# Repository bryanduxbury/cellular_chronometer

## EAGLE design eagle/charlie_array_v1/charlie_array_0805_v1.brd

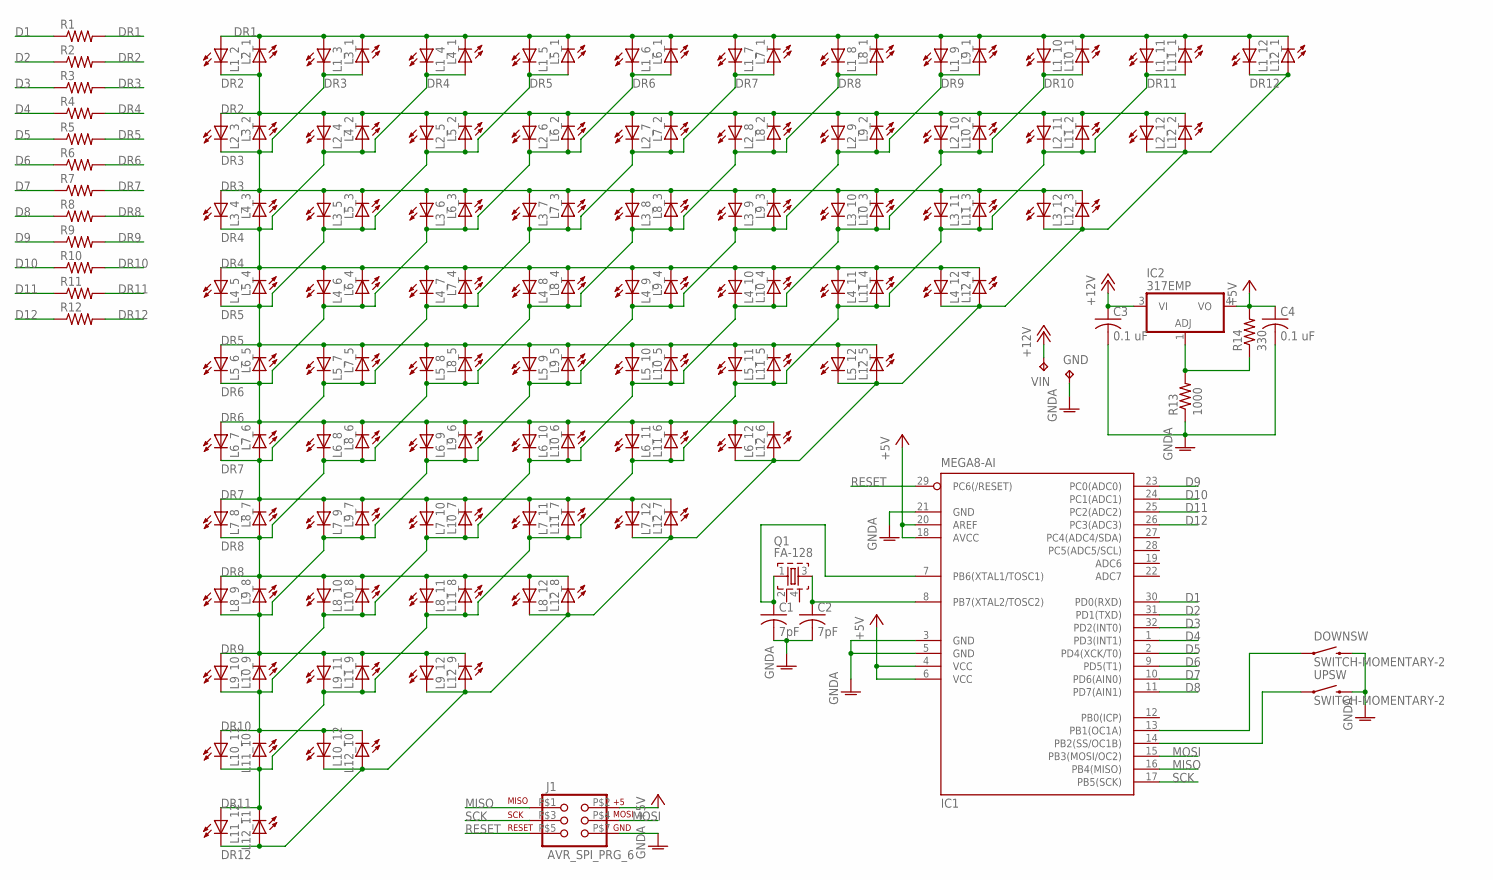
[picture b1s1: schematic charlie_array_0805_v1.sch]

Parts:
C1, C2: 7pF; C0603
C3, C4: 0.1 uF; C0603
DOWNSW: SWITCH-MOMENTARY-2; TACTILE_SWITCH_TALL
GND: TPTP20SQ; TP20SQ
IC1: MEGA8-AI; TQFP32-08
IC2: 317EMP; SOT223
J1: AVR_SPI_PRG_6; 2X3_ICSP_SMD
L1_2, L1_3, L1_4, L1_5, L1_6, L1_7, L1_8, L1_9, L1_10, L1_11, L1_12, L2_1, L2_3, L2_4, L2_5, L2_6, L2_7, L2_8, L2_9, L2_10, L2_11, L2_12, L3_1, L3_2, L3_4, L3_5, L3_6, L3_7, L3_8, L3_9, L3_10, L3_11, L3_12, L4_1, L4_2, L4_3, L4_5, L4_6, L4_7, L4_8, L4_9, L4_10, L4_11, L4_12, L5_1, L5_2, L5_3, L5_4, L5_6, L5_7, L5_8, L5_9, L5_10, L5_11, L5_12, L6_1, L6_2, L6_3, L6_4, L6_5, L6_7, L6_8, L6_9, L6_10, L6_11, L6_12, L7_1, L7_2, L7_3, L7_4, L7_5, L7_6, L7_8, L7_9, L7_10, L7_11, L7_12, L8_1, L8_2, L8_3, L8_4, L8_5, L8_6, L8_7, L8_9, L8_10, L8_11, L8_12, L9_1, L9_2, L9_3, L9_4, L9_5, L9_6, L9_7, L9_8, L9_10, L9_11, L9_12, L10_1, L10_2, L10_3, L10_4, L10_5, L10_6, L10_7, L10_8, L10_9, L10_11, L10_12, L11_1, L11_2, L11_3, L11_4, L11_5, L11_6, L11_7, L11_8, L11_9, L11_10, L11_12, L12_1, L12_2, L12_3, L12_4, L12_5, L12_6, L12_7, L12_8, L12_9, L12_10, L12_11: LEDCHIPLED_0805; CHIPLED_0805
Q1: FA-128
R1, R2, R3, R4, R5, R6, R7, R8, R9, R10, R11, R12: R-US_R0603; R0603
R13: 1000; R0603
R14: 330; R0603
UPSW: SWITCH-MOMENTARY-2; TACTILE_SWITCH_TALL
VIN: TPTP20SQ; TP20SQ

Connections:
+5V: C4.1, IC1.4 (VCC), IC1.6 (VCC), IC1.18 (AVCC), IC1.20 (AREF), IC2.4 (VO), J1.P$2 (2), R14.2
+12V: C3.1, IC2.3 (VI), VIN.TP
D1: IC1.30 (PD0(RXD)), R1.1
D2: IC1.31 (PD1(TXD)), R2.1
D3: IC1.32 (PD2(INT0)), R3.1
D4: IC1.1 (PD3(INT1)), R4.1
D5: IC1.2 (PD4(XCK/T0)), R5.1
D6: IC1.9 (PD5(T1)), R6.1
D7: IC1.10 (PD6(AIN0)), R7.1
D8: IC1.11 (PD7(AIN1)), R8.1
D9: IC1.23 (PC0(ADC0)), R9.1
D10: IC1.24 (PC1(ADC1)), R10.1
D11: IC1.25 (PC2(ADC2)), R11.1
D12: IC1.26 (PC3(ADC3)), R12.1
DR1: L1_2.A, L1_3.A, L1_4.A, L1_5.A, L1_6.A, L1_7.A, L1_8.A, L1_9.A, L1_10.A, L1_11.A, L1_12.A, L2_1.C, L3_1.C, L4_1.C, L5_1.C, L6_1.C, L7_1.C, L8_1.C, L9_1.C, L10_1.C, L11_1.C, L12_1.C, R1.2
DR2: L1_2.C, L2_1.A, L2_3.A, L2_4.A, L2_5.A, L2_6.A, L2_7.A, L2_8.A, L2_9.A, L2_10.A, L2_11.A, L2_12.A, L3_2.C, L4_2.C, L5_2.C, L6_2.C, L7_2.C, L8_2.C, L9_2.C, L10_2.C, L11_2.C, L12_2.C, R2.2
DR3: L1_3.C, L2_3.C, L3_1.A, L3_2.A, L3_4.A, L3_5.A, L3_6.A, L3_7.A, L3_8.A, L3_9.A, L3_10.A, L3_11.A, L3_12.A, L4_3.C, L5_3.C, L6_3.C, L7_3.C, L8_3.C, L9_3.C, L10_3.C, L11_3.C, L12_3.C, R3.2
DR4: L1_4.C, L2_4.C, L3_4.C, L4_1.A, L4_2.A, L4_3.A, L4_5.A, L4_6.A, L4_7.A, L4_8.A, L4_9.A, L4_10.A, L4_11.A, L4_12.A, L5_4.C, L6_4.C, L7_4.C, L8_4.C, L9_4.C, L10_4.C, L11_4.C, L12_4.C, R4.2
DR5: L1_5.C, L2_5.C, L3_5.C, L4_5.C, L5_1.A, L5_2.A, L5_3.A, L5_4.A, L5_6.A, L5_7.A, L5_8.A, L5_9.A, L5_10.A, L5_11.A, L5_12.A, L6_5.C, L7_5.C, L8_5.C, L9_5.C, L10_5.C, L11_5.C, L12_5.C, R5.2
DR6: L1_6.C, L2_6.C, L3_6.C, L4_6.C, L5_6.C, L6_1.A, L6_2.A, L6_3.A, L6_4.A, L6_5.A, L6_7.A, L6_8.A, L6_9.A, L6_10.A, L6_11.A, L6_12.A, L7_6.C, L8_6.C, L9_6.C, L10_6.C, L11_6.C, L12_6.C, R6.2
DR7: L1_7.C, L2_7.C, L3_7.C, L4_7.C, L5_7.C, L6_7.C, L7_1.A, L7_2.A, L7_3.A, L7_4.A, L7_5.A, L7_6.A, L7_8.A, L7_9.A, L7_10.A, L7_11.A, L7_12.A, L8_7.C, L9_7.C, L10_7.C, L11_7.C, L12_7.C, R7.2
DR8: L1_8.C, L2_8.C, L3_8.C, L4_8.C, L5_8.C, L6_8.C, L7_8.C, L8_1.A, L8_2.A, L8_3.A, L8_4.A, L8_5.A, L8_6.A, L8_7.A, L8_9.A, L8_10.A, L8_11.A, L8_12.A, L9_8.C, L10_8.C, L11_8.C, L12_8.C, R8.2
DR9: L1_9.C, L2_9.C, L3_9.C, L4_9.C, L5_9.C, L6_9.C, L7_9.C, L8_9.C, L9_1.A, L9_2.A, L9_3.A, L9_4.A, L9_5.A, L9_6.A, L9_7.A, L9_8.A, L9_10.A, L9_11.A, L9_12.A, L10_9.C, L11_9.C, L12_9.C, R9.2
DR10: L1_10.C, L2_10.C, L3_10.C, L4_10.C, L5_10.C, L6_10.C, L7_10.C, L8_10.C, L9_10.C, L10_1.A, L10_2.A, L10_3.A, L10_4.A, L10_5.A, L10_6.A, L10_7.A, L10_8.A, L10_9.A, L10_11.A, L10_12.A, L11_10.C, L12_10.C, R10.2
DR11: L1_11.C, L2_11.C, L3_11.C, L4_11.C, L5_11.C, L6_11.C, L7_11.C, L8_11.C, L9_11.C, L10_11.C, L11_1.A, L11_2.A, L11_3.A, L11_4.A, L11_5.A, L11_6.A, L11_7.A, L11_8.A, L11_9.A, L11_10.A, L11_12.A, L12_11.C, R11.2
DR12: L1_12.C, L2_12.C, L3_12.C, L4_12.C, L5_12.C, L6_12.C, L7_12.C, L8_12.C, L9_12.C, L10_12.C, L11_12.C, L12_1.A, L12_2.A, L12_3.A, L12_4.A, L12_5.A, L12_6.A, L12_7.A, L12_8.A, L12_9.A, L12_10.A, L12_11.A, R12.2
GNDA: C1.2, C2.2, C3.2, C4.2, DOWNSW.B2 (2), GND.TP, IC1.3 (GND), IC1.5 (GND), IC1.21 (GND), J1.P$7 (6), R13.1, UPSW.B2 (2)
MISO: IC1.16 (PB4(MISO)), J1.P$1 (1)
MOSI: IC1.15 (PB3(MOSI/OC2)), J1.P$4 (4)
unnamed: C2.1, IC1.8 (PB7(XTAL2/TOSC2)), Q1.3
unnamed: IC1.14 (PB2(SS/OC1B)), UPSW.A2 (1)
unnamed: DOWNSW.A2 (1), IC1.13 (PB1(OC1A))
unnamed: C1.1, IC1.7 (PB6(XTAL1/TOSC1)), Q1.1
unnamed: IC2.1 (ADJ), R13.2, R14.1
RESET: IC1.29 (PC6(/RESET)), J1.P$5 (5)
SCK: IC1.17 (PB5(SCK)), J1.P$3 (3)

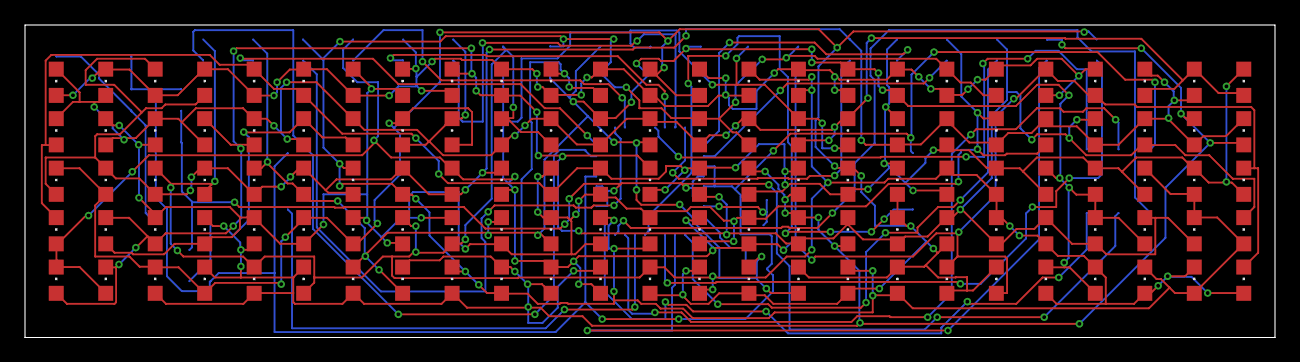
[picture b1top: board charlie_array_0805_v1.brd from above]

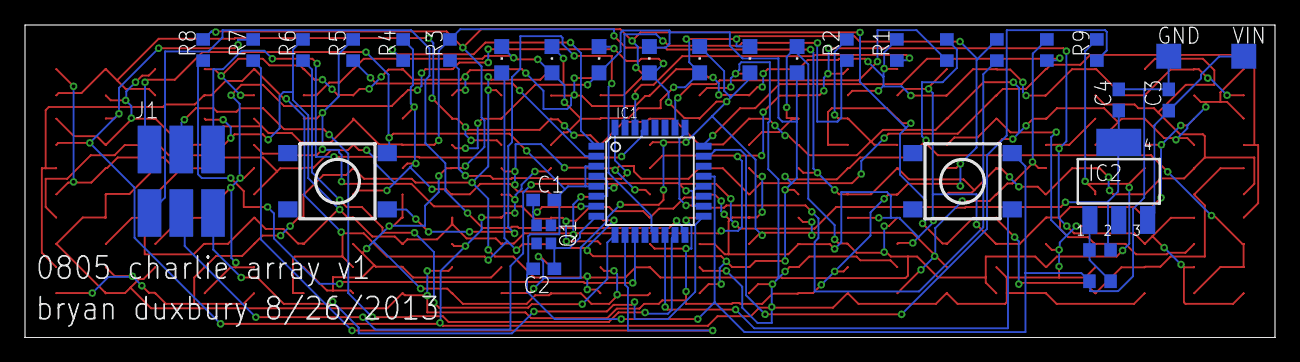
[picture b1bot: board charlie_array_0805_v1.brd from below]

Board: 2 copper layers, 100.0 x 25.0 mm, 158 parts (33 on the bottom side), 36 nets.

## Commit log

2013-07-02 init commit
2013-07-09 game of life prototype
2013-07-09 break out grid from proto, progress towards exploring for one prior generation
2013-07-10 added spec for basic grid behaviors; improved next_generation runtime by about 10x
2013-07-18 first stab at a genetic algo version of the predecessor search
2013-07-27 most of a working duparc predecessor searcher
2013-07-29 mostly? fixed a logical error in identifying the top row predecessors
2013-07-31 kinda working... making progress anyways
2013-07-31 nail down attributes of bounded/extra ataviser
2013-08-02 major improvements, particularly the intersecting row ataviser
2013-08-04 generated patterns for the narrow font
2013-08-04 add bitvector related stuff to Pt class
2013-08-04 mostly refactored on Pt methods
2013-08-04 gitignore time
2013-08-04 further refactorign
2013-08-05 searcher getting closer to working
2013-08-05 regen patterns
2013-08-05 don't need patterns.rb
2013-08-09 woo, have a full working display set
2013-08-13 lots of progress on chronomata sketch
2013-08-13 remove unused include
2013-08-16 added initial scad prototype, cleaned up some logic in sketch
2013-08-26 add gitignore
2013-08-26 eagle files v1
2013-08-26 adjusted to fit in 100mm width
2013-08-26 don't need these export files committed
2013-09-21 working out issues on the new hardware
2013-09-22 incremental progress
2013-09-27 figured out a bug in living_neighbors
2013-09-27 regen'd 2 back
2013-09-27 progress on firmware
2013-09-29 switched over to 32 bit masking instead of crazy looping
2013-10-02 remove concept of 'extra width' from row atavisers
2013-10-02 fix intersecting row ataviser spec
2013-10-02 incremental progress on enclosure design
2013-10-02 fix DuparcAtaviser to remove extra
2013-10-02 fix hierarchical duparc ataviser to remove extra
2013-10-08 changes to make search for toroidal grids; also, some performance improvements
2013-10-10 making first increments of progress on java version of ataviser
2013-10-11 some logging experiments in ruby search codebase
2013-10-11 java WIP
2013-10-12 closer to mimicking the ruby version of hierarchical ataviser
2013-10-12 add support for SolutionFilter
2013-10-12 test performance with TubularRowFilter
2013-10-12 add a little commenting to the core algorithm, and add smarter intermediate limiting
2013-10-12 add solution limiters
2013-10-12 oops, didn't want those compiled artifacts checked in at all
2013-10-12 move some stuff around in packages
2013-10-12 more repackaging
2013-10-13 introduce Grid class, modify everything to work with that
2013-10-13 oh yeah, RowAtaviser caching is important
2013-10-13 adding testing capabilities to Grid
2013-10-16 forward
2013-10-16 debugging through the issues with ruby toroidal solver
2013-10-17 experimenting with retaining many more intermediate solutions
2013-10-19 repackage... well, everything
2013-10-21 firmware progress
2013-10-23 cleaning up the firmware, ready to actually be tested
2013-10-23 all the ataviser's hard work
2013-10-23 don't need all the individual back_ files
2013-10-24 latest refactoring in ataviser
2013-10-26 fixed the issues with toroidal life (it's working now)
2013-10-26 extract a function
2013-10-26 clean up some cruft; latch the 'next state' button so it doesn't run faster than humans can see
2013-10-27 prototypes for nice linear fade in/out and crossfade effects
2013-10-27 gitignore .DS_Store
2013-10-27 remove some cruft; add the real deal method for advancing the clock minute by minute
2013-10-28 get rid of all the __back_* files
2013-10-28 recompute the goofed up 0100 priors
2013-10-28 fixed version of 01_00
2013-10-29 fixed conflict
2013-10-29 draft of seekUp() behavior
2013-10-29 woohoo, setting time through button press is working
2013-10-29 off by one error in fastMinuteDisplay
2013-10-29 added seekDown behavior
2013-10-29 get rid of the test driver loop
2013-10-30 oops, had a bug in seekDown()
2013-10-30 don't need this file anymore
2013-10-30 few little things to make display marginally faster
2013-10-30 remove the clear() call inside fastDisplayMinute to take away the display flicker when seeking
2013-10-30 inline the incrementMinute function, since it's only used in one place
2013-10-30 remove the num priors blob, since we no longer need that; remove supporting and test functions
2013-10-30 remove unnecessary cast
2013-10-30 enable all the states
2013-10-30 fix some weird code formatting
2013-11-05 switch to a millis() based tick generator; remove cruft left over from other implementation
2014-01-09 enclosure wip
2014-01-11 looks like a good completed draft of the suspended enclosure
2014-01-12 narrow down the cord slot slightly
2014-01-18 add top-level rotate for animated gif
2014-01-30 adjust all the tab widths to (hopefully) get a decent interference fit
2014-02-02 everything
2014-02-02 adjusted a number of parameters to make the pieces fit together better
2014-02-03 rotate the switches to point out; clean up whitespace and unused code; add a todo
2014-02-06 fix the switch height parameter so the buttons will actually touch correctly; notch out the bottom piece slightly so the cord doesn't have such a sharp bend
2014-02-06 double the speed of the 'fast mode' time setting
2014-02-09 start the clock at 12; normalize the delays across the board; make the time-setting faster
2015-08-22 woohoo new grid ataviser implementation
2015-08-25 performance improvements and monitoring added to MinGrowthAtaviser
2015-08-31 WIP RowSplittingAtaviser

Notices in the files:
parts and their libraries:
SparkFun: Licensing: CC v3.0 Share-Alike You are welcome to use this library for commercial purposes.
